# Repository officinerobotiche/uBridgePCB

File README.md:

# ![Officine Robotiche][Logo] uBridge PCB
**The first DC motor board in 4cm X 4cm** - PCB boards for uBridge

This is a project in development by [Officine Robotiche] team.

###Join on open firmware project [uNAV.X](https://github.com/officinerobotiche/uNAV.X)!!!

# Hardware features
- 2 x A4950 Full-Bridge DMOS PWM Motor Driver
  - Up to 3,5A and 40V input ( limited at 23V if used with uNav )
  - Short circuit protected
  - Over Temperature protected
- 2 x ACS712 Hall Effect-Based Linear Current Sensor IC
  - ±5A Full-Scale input Range with 185mV/A variation
  - 2,5V output @ 0.0A
- 2 connector for Encoder with Gnd, Vcc, ChA, ChB, Chz signal.
- 4 LED on outupt of H-Bridge.
- Protection diode on input.
- size: 4cm x 4cm uNav stackable.
- Matrix board with holes 2.54mm compliant.

# Available Shields
- [uNav](https://github.com/officinerobotiche/uNAVPCB)
- [uMatrix](https://github.com/officinerobotiche/)

[Officine Robotiche]:http://www.officinerobotiche.it/
[Logo]:http://2014.officinerobotiche.it/wp-content/uploads/sites/4/2014/09/ORlogoSimpleSmall.png

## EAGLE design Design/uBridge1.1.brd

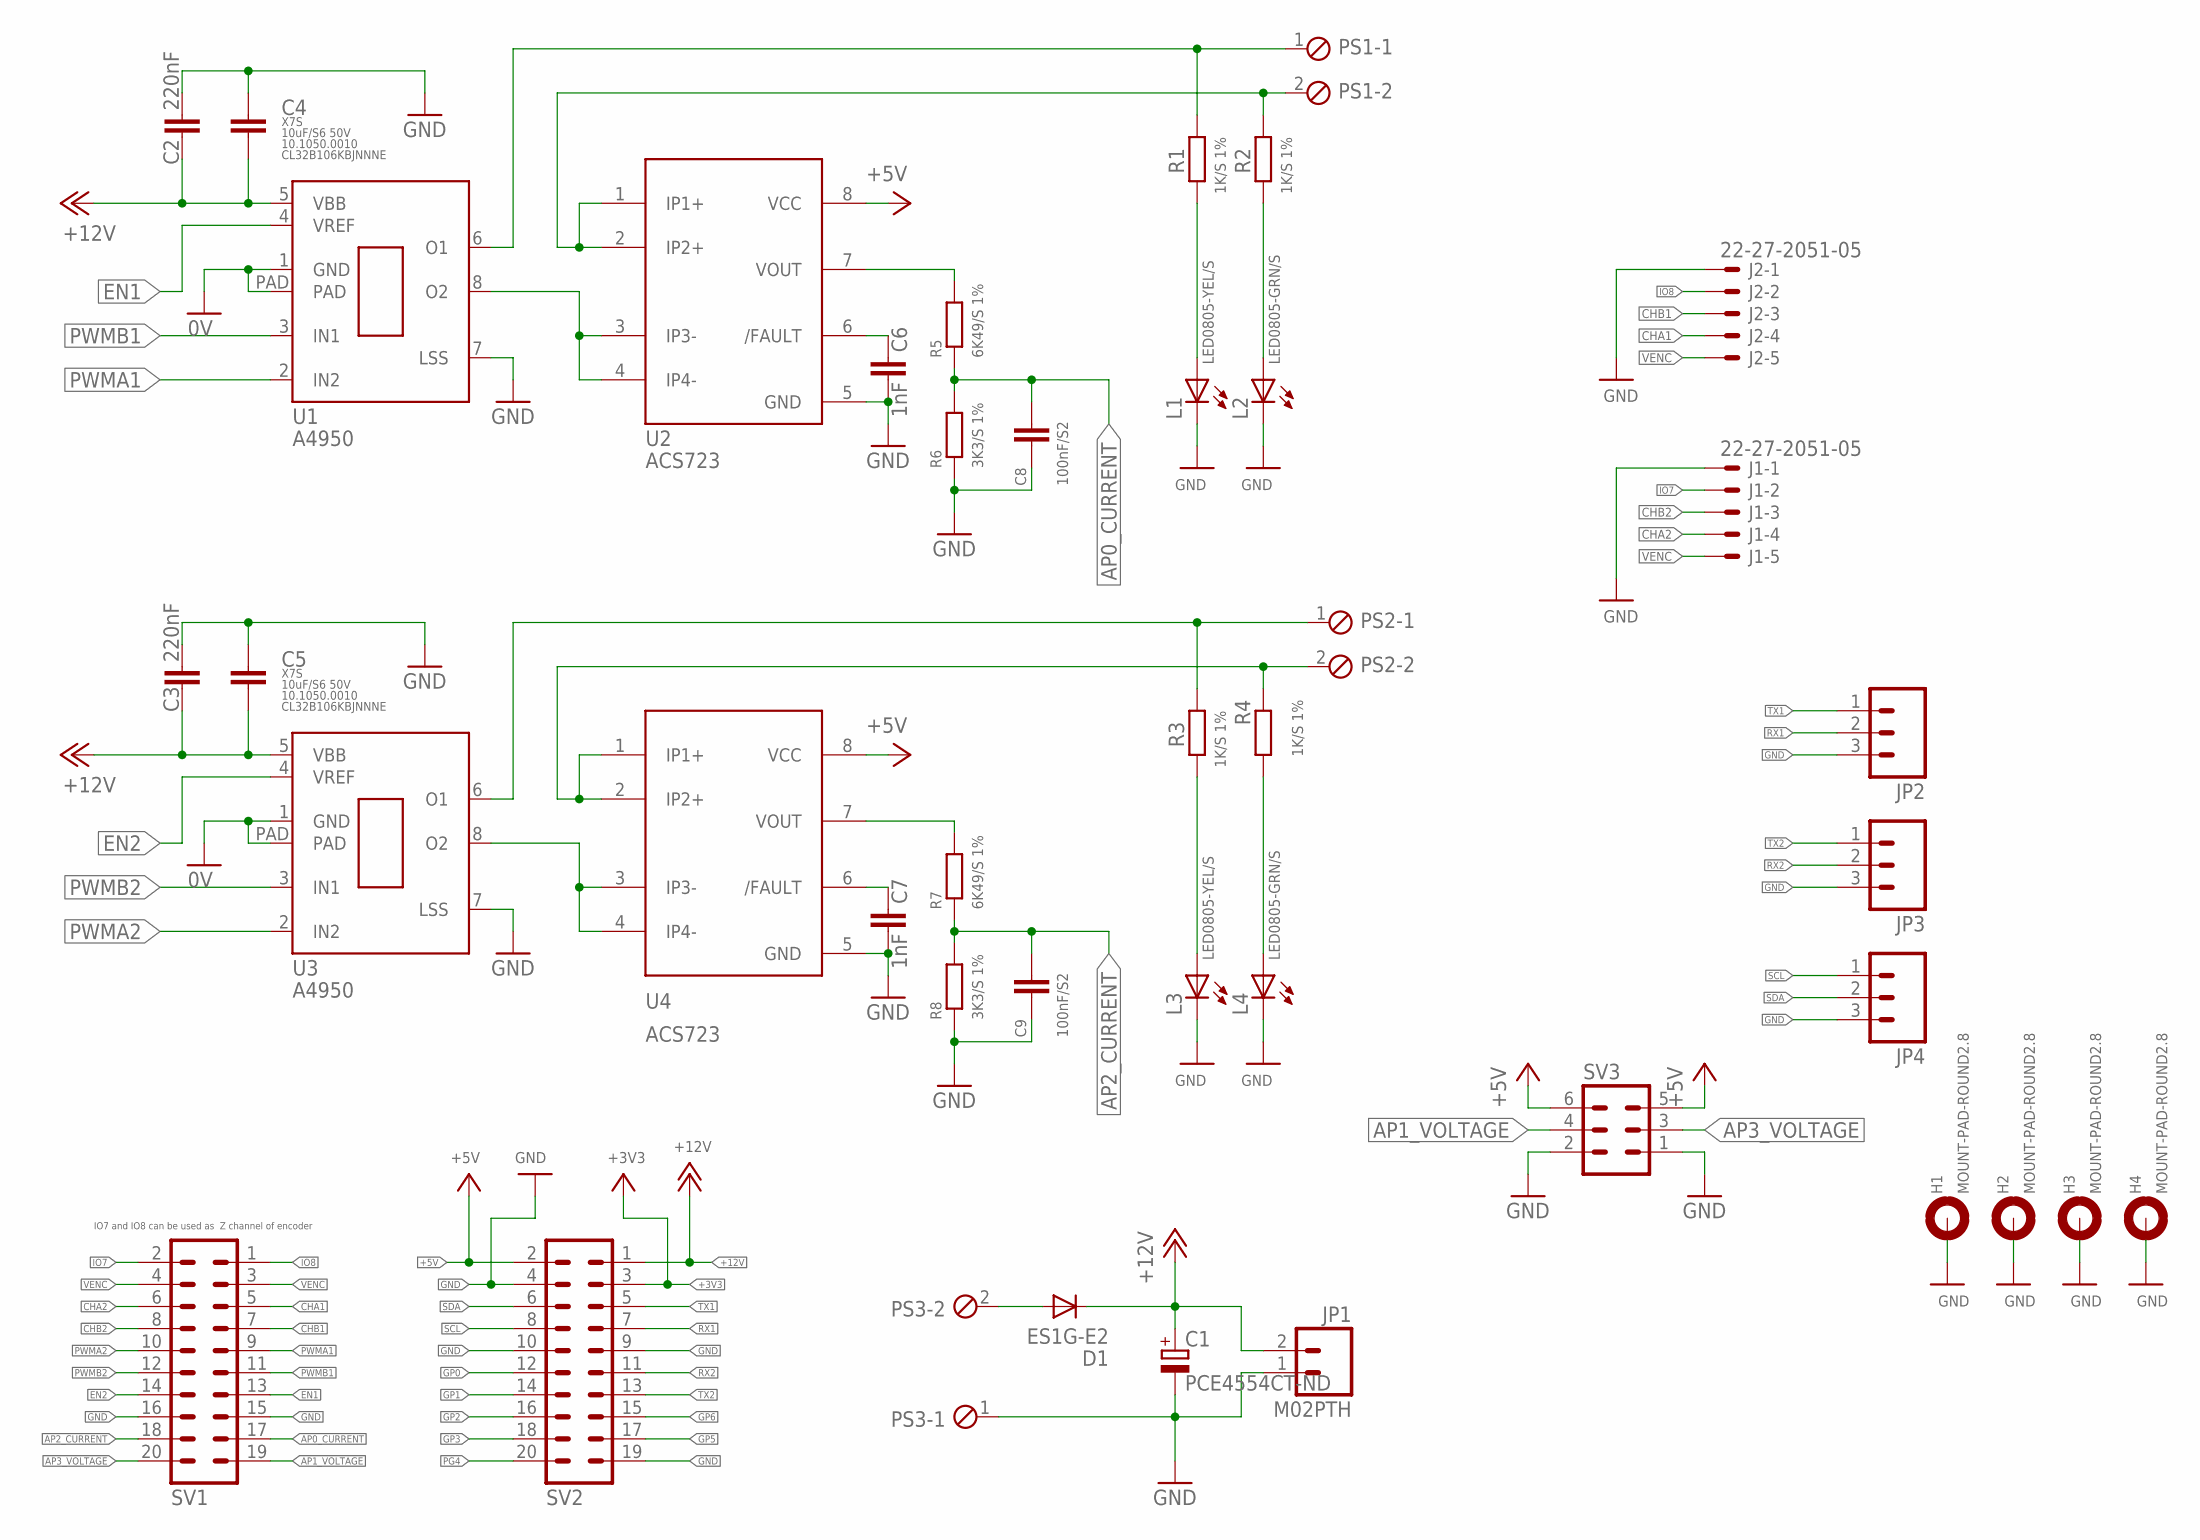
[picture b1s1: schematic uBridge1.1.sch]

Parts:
C1: PCE4554CT-ND; UD-6,3X7,7_NICHICON
C2, C3: 220nF; C0805K
C4, C5: 10uF/S6 50V; C3225
C6, C7: 1nF; C0805K
C8, C9: 100nF/S2; C0603
D1: ES1G-E2; DO214BA
H1, H2, H3, H4: MOUNT-PAD-ROUND2.8; 2,8-PAD
J1, J2: 22-27-2051-05; 6410-05
JP1: M02PTH; 1X02
JP2, JP3, JP4: M03PTH; 1X03
L1, L3: LED0805-YEL/S; CHIPLED_0805
L2, L4: LED0805-GRN/S; CHIPLED_0805
PS1, PS2, PS3: MPT2; 2POL254
R1, R2, R3, R4: 1K/S 1%; R0603
R5, R7: 6K49/S 1%; R0603
R6, R8: 3K3/S 1%; R0603
SV1, SV2: MA10-2
SV3: MA03-2
U1, U3: A4950; 8SOICN
U2, U4: ACS723; SO08

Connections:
+3V3: SV2.3
+5V: SV2.2, SV3.5, SV3.6, U2.8 (VCC), U4.8 (VCC)
+12V: C1.+, C2.2, C3.2, C4.2, C5.2, D1.C, JP1.2, SV2.1, U1.5 (VBB), U3.5 (VBB)
AP0_CURRENT: C8.1, R5.1, R6.2, SV1.17
AP1_VOLTAGE: SV1.19, SV3.4
AP2_CURRENT: C9.1, R7.1, R8.2, SV1.18
AP3_VOLTAGE: SV1.20, SV3.3
CHA1: J2.4, SV1.5
CHA2: J1.4, SV1.6
CHB1: J2.3, SV1.7
CHB2: J1.3, SV1.8
EN1: SV1.13, U1.4 (VREF)
EN2: SV1.14, U3.4 (VREF)
GND: C1.-, C2.1, C3.1, C4.1, C5.1, C6.2, C7.2, C8.2, C9.2, H1.B2,8, H2.B2,8, H3.B2,8, H4.B2,8, J1.1, J2.1, JP1.1, JP2.3, JP3.3, JP4.3, L1.C, L2.C, L3.C, L4.C, PS3.1, R6.1, R8.1, SV1.15, SV1.16, SV2.4, SV2.9, SV2.10, SV2.19, SV3.1, SV3.2, U1.1 (GND), U1.7 (LSS), U1.PAD, U2.5 (GND), U3.1 (GND), U3.7 (LSS), U3.PAD, U4.5 (GND)
GP0: SV2.12
GP1: SV2.14
GP2: SV2.16
GP3: SV2.18
GP5: SV2.17
GP6: SV2.15
IO7: J1.2, SV1.2
IO8: J2.2, SV1.1
unnamed: D1.A, PS3.2
unnamed: L1.A, R1.2
unnamed: L2.A, R2.2
unnamed: U1.8 (O2), U2.3 (IP3-), U2.4 (IP4-)
unnamed: R5.2, U2.7 (VOUT)
unnamed: U3.8 (O2), U4.3 (IP3-), U4.4 (IP4-)
unnamed: PS1.2, R2.1, U2.1 (IP1+), U2.2 (IP2+)
unnamed: PS2.2, R4.1, U4.1 (IP1+), U4.2 (IP2+)
unnamed: PS1.1, R1.1, U1.6 (O1)
unnamed: PS2.1, R3.1, U3.6 (O1)
unnamed: C6.1, U2.6 (/FAULT)
unnamed: C7.1, U4.6 (/FAULT)
unnamed: R7.2, U4.7 (VOUT)
PG4: SV2.20
PWMA1: SV1.9, U1.2 (IN2)
PWMA2: SV1.10, U3.2 (IN2)
PWMB1: SV1.11, U1.3 (IN1)
PWMB2: SV1.12, U3.3 (IN1)
RX1: JP2.2, SV2.7
RX2: JP3.2, SV2.11
SCL: JP4.1, SV2.8
SDA: JP4.2, SV2.6
TX1: JP2.1, SV2.5
TX2: JP3.1, SV2.13
VENC: J1.5, J2.5, SV1.3, SV1.4
VENC1-LD3: L3.A, R3.2
VENC2-LD4: L4.A, R4.2

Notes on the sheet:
IO7 and IO8 can be used as Z channel of encoder

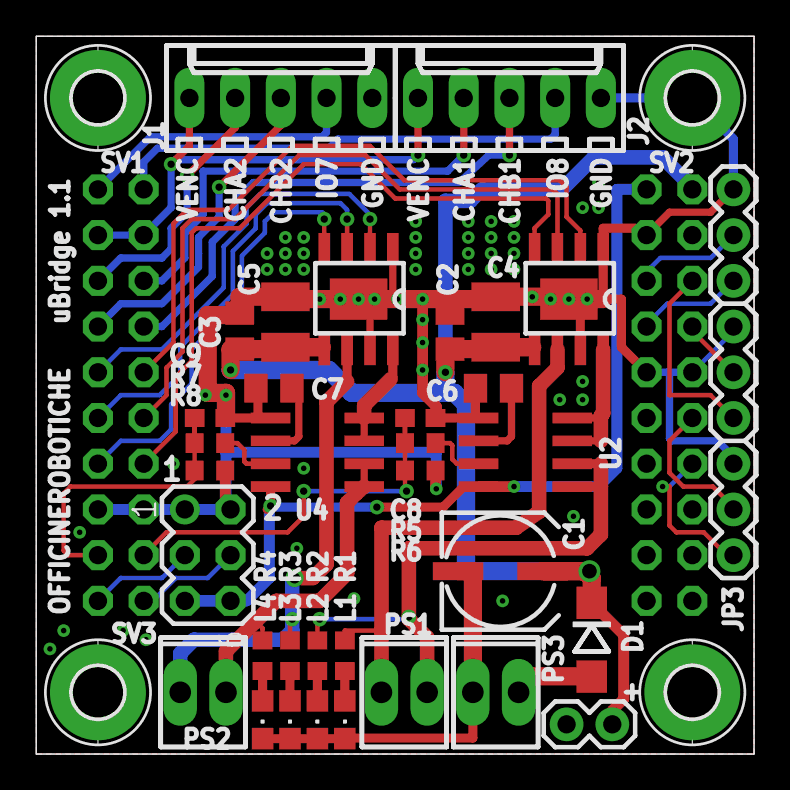
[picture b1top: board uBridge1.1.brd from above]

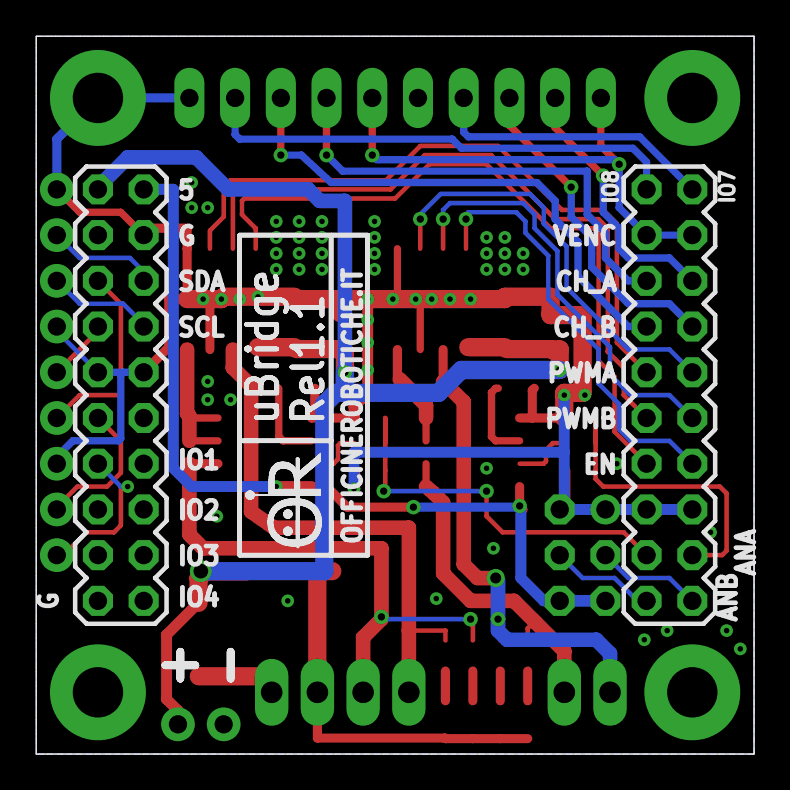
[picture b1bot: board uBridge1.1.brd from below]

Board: 2 copper layers, 39.9 x 39.9 mm, 42 parts (2 on the bottom side), 41 nets.

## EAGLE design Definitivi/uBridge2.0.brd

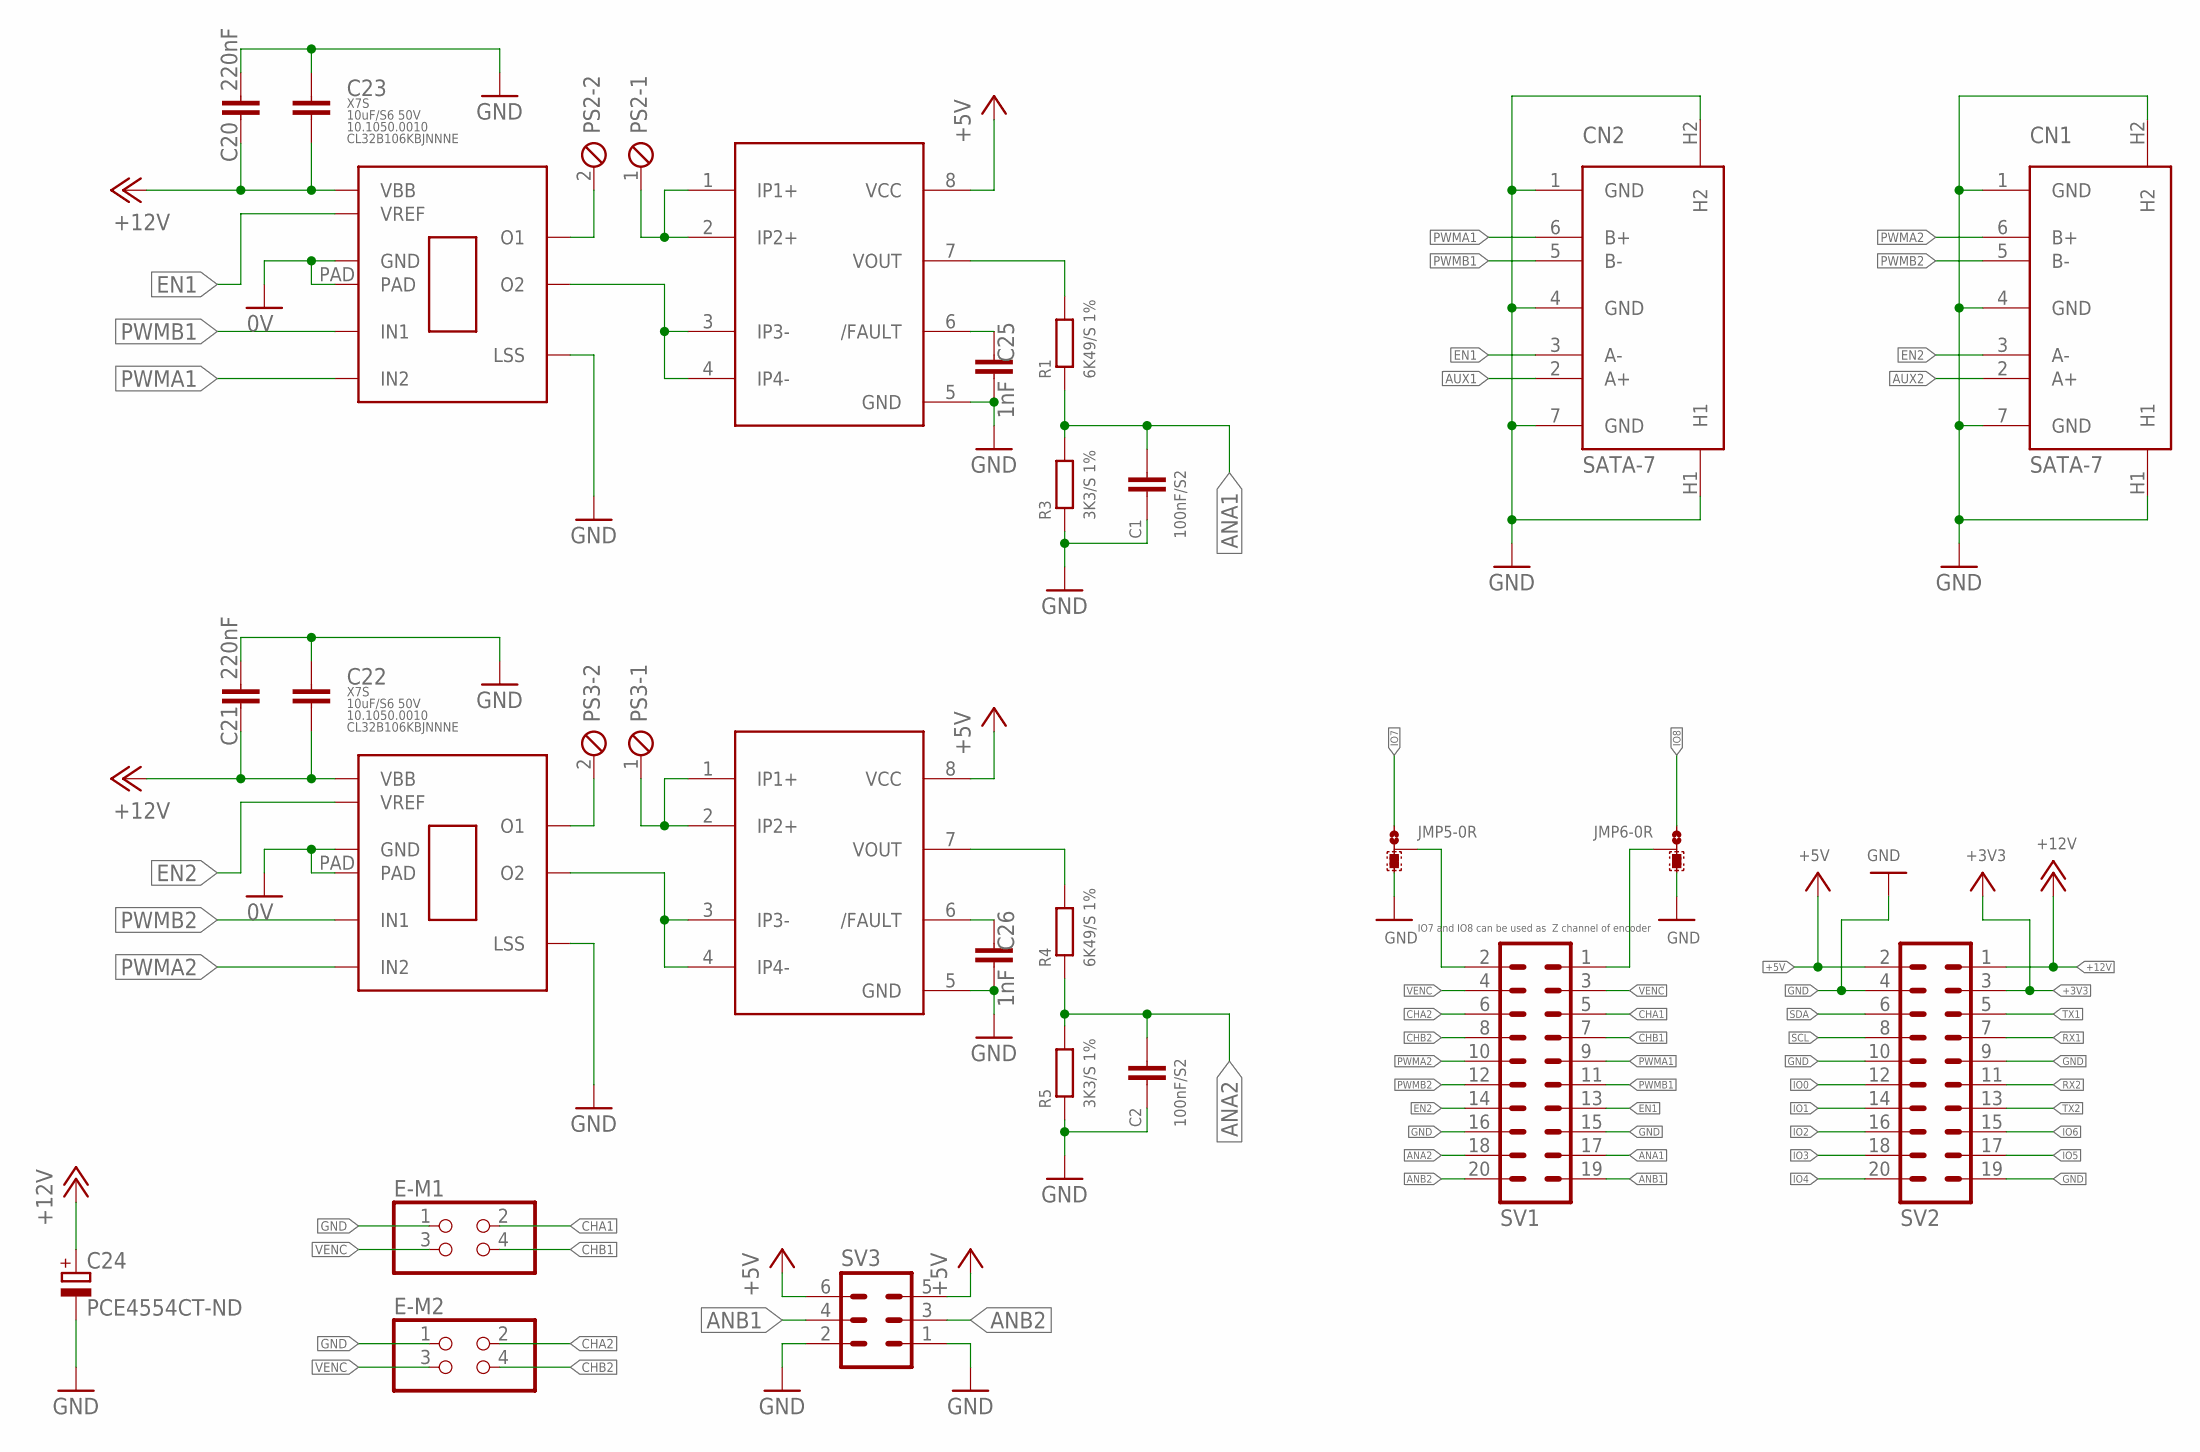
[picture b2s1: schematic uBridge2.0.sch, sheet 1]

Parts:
C1, C2: 100nF/S2; C0603
C20, C21: 220nF; C0805K
C22, C23: 10uF/S6 50V; C3225
C24: PCE4554CT-ND; UD-6,3X7,7_NICHICON
C25, C26: 1nF; C0805K
CN1, CN2: SATA-7; SATA-5607-5102-SH
E-M1, E-M2: PINHD-2X2; 2X02
JMP5, JMP6: 0R-JUMPC; C0R-JMP
PS2, PS3: MPT2; 2POL254
R1, R4: 6K49/S 1%; R0603
R3, R5: 3K3/S 1%; R0603
SV1, SV2: MA10-2
SV3: MA03-2
U$2, U$3: A4950; SOICN
U$4, U$5: ACS723; SO08

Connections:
+3V3: SV2.3
+5V: SV2.2, SV3.5, SV3.6, U$4.8 (VCC), U$5.8 (VCC); also elsewhere on the board
+12V: C20.2, C21.2, C22.2, C23.2, C24.+, SV2.1, U$2.5VCC (VBB), U$3.5VCC (VBB); also elsewhere on the board
ANA1: C1.1, R1.1, R3.2, SV1.17
ANA2: C2.1, R4.1, R5.2, SV1.18
ANB1: SV1.19, SV3.4
ANB2: SV1.20, SV3.3
AUX1: CN2.2 (A+)
AUX2: CN1.2 (A+)
CHA1: E-M1.2, SV1.5
CHA2: E-M2.2, SV1.6
CHB1: E-M1.4, SV1.7
CHB2: E-M2.4, SV1.8
EN1: CN2.3 (A-), SV1.13, U$2.4CS (VREF)
EN2: CN1.3 (A-), SV1.14, U$3.4CS (VREF)
GND: C1.2, C2.2, C20.1, C21.1, C22.1, C23.1, C24.-, C25.2, C26.2, CN1.1 (GND), CN1.4 (GND), CN1.7 (GND), CN1.H1, CN1.H2, CN2.1 (GND), CN2.4 (GND), CN2.7 (GND), CN2.H1, CN2.H2, E-M1.1, E-M2.1, JMP5.3, JMP6.3, R3.1, R5.1, SV1.15, SV1.16, SV2.4, SV2.9, SV2.10, SV2.19, SV3.1, SV3.2, U$2.1VIN (GND), U$2.7BOOT (LSS), U$2.PAD, U$3.1VIN (GND), U$3.7BOOT (LSS), U$3.PAD, U$4.5 (GND), U$5.5 (GND); also elsewhere on the board
IO0: SV2.12
IO1: SV2.14
IO2: SV2.16
IO3: SV2.18
IO4: SV2.20
IO5: SV2.17
IO6: SV2.15
IO7: JMP5.1
IO8: JMP6.1
unnamed: R1.2, U$4.7 (VOUT)
unnamed: R4.2, U$5.7 (VOUT)
unnamed: JMP5.2, SV1.2
unnamed: U$2.8SW (O2), U$4.3 (IP3-), U$4.4 (IP4-)
unnamed: U$3.8SW (O2), U$5.3 (IP3-), U$5.4 (IP4-)
unnamed: PS2.1, U$4.1 (IP1+), U$4.2 (IP2+)
unnamed: JMP6.2, SV1.1
unnamed: PS3.1, U$5.1 (IP1+), U$5.2 (IP2+)
unnamed: PS2.2, U$2.6GND (O1)
unnamed: PS3.2, U$3.6GND (O1)
unnamed: C25.1, U$4.6 (/FAULT)
unnamed: C26.1, U$5.6 (/FAULT)
PWMA1: CN2.6 (B+), SV1.9, U$2.2TON (IN2)
PWMA2: CN1.6 (B+), SV1.10, U$3.2TON (IN2)
PWMB1: CN2.5 (B-), SV1.11, U$2.3EN (IN1)
PWMB2: CN1.5 (B-), SV1.12, U$3.3EN (IN1)
RX1: SV2.7
RX2: SV2.11
SCL: SV2.8
SDA: SV2.6
TX1: SV2.5
TX2: SV2.13
VENC: E-M1.3, E-M2.3, SV1.3, SV1.4

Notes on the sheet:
IO7 and IO8 can be used as Z channel of encoder

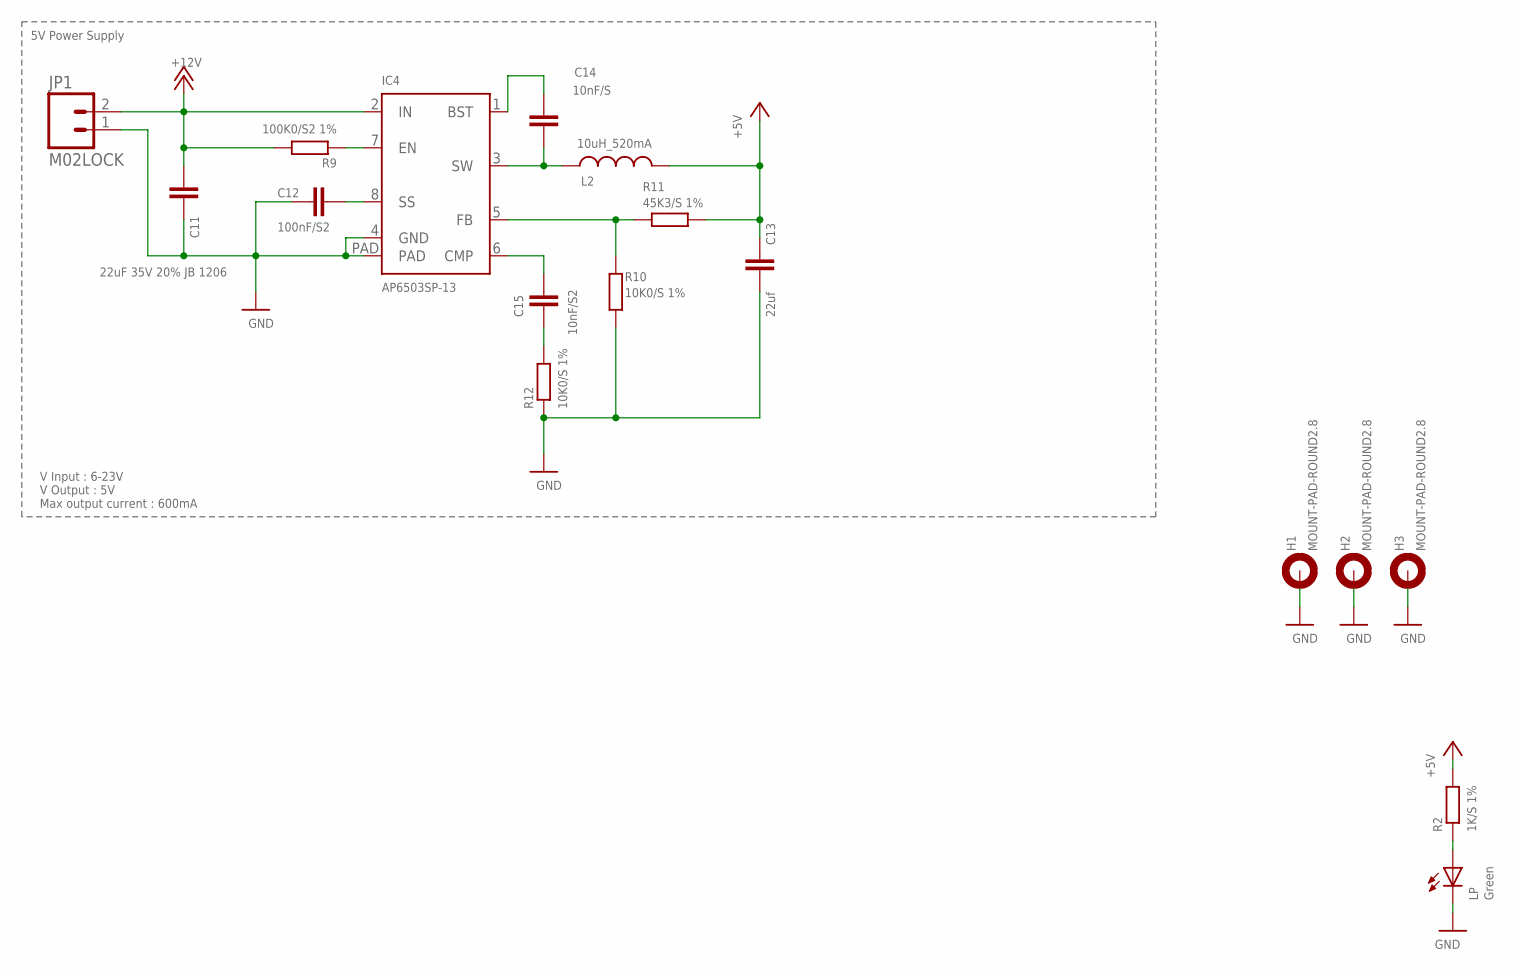
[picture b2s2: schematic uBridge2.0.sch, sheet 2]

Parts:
C11: 22uF 35V 20% JB 1206; C1206
C12: 100nF/S2; C0603
C13: 22uf; C1206
C14: 10nF/S; C0603
C15: 10nF/S2; C0603
H1, H2, H3: MOUNT-PAD-ROUND2.8; 2,8-PAD
IC4: AP6503SP-13; SO-8EP
JP1: M02LOCK; 1X02_LOCK
L2: 10uH_520mA; 1210
LP: Green; CHIPLED_0805
R2: 1K/S 1%; R0603
R9: 100K0/S2 1%; R0603
R10, R12: 10K0/S 1%; R0603
R11: 45K3/S 1%; R0603

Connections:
+5V: C13.1, L2.2, R2.2, R11.2; also elsewhere on the board
+12V: C11.1, IC4.2 (IN), JP1.2, R9.2; also elsewhere on the board
GND: C11.2, C12.2, C13.2, H1.B2,8, H2.B2,8, H3.B2,8, IC4.4 (GND), IC4.PAD, JP1.1, LP.C, R10.2, R12.1; also elsewhere on the board
unnamed: C14.1, IC4.1 (BST)
unnamed: LP.A, R2.1
unnamed: IC4.7 (EN), R9.1
unnamed: C12.1, IC4.8 (SS)
unnamed: IC4.5 (FB), R10.1, R11.1
unnamed: C14.2, IC4.3 (SW), L2.1
unnamed: C15.1, IC4.6 (CMP)
unnamed: C15.2, R12.2

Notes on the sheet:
5V Power Supply
V Input : 6-23V V Output : 5V Max output current : 600mA

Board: 2 copper layers, 45 parts (4 on the bottom side), 38 nets, no tracks yet.

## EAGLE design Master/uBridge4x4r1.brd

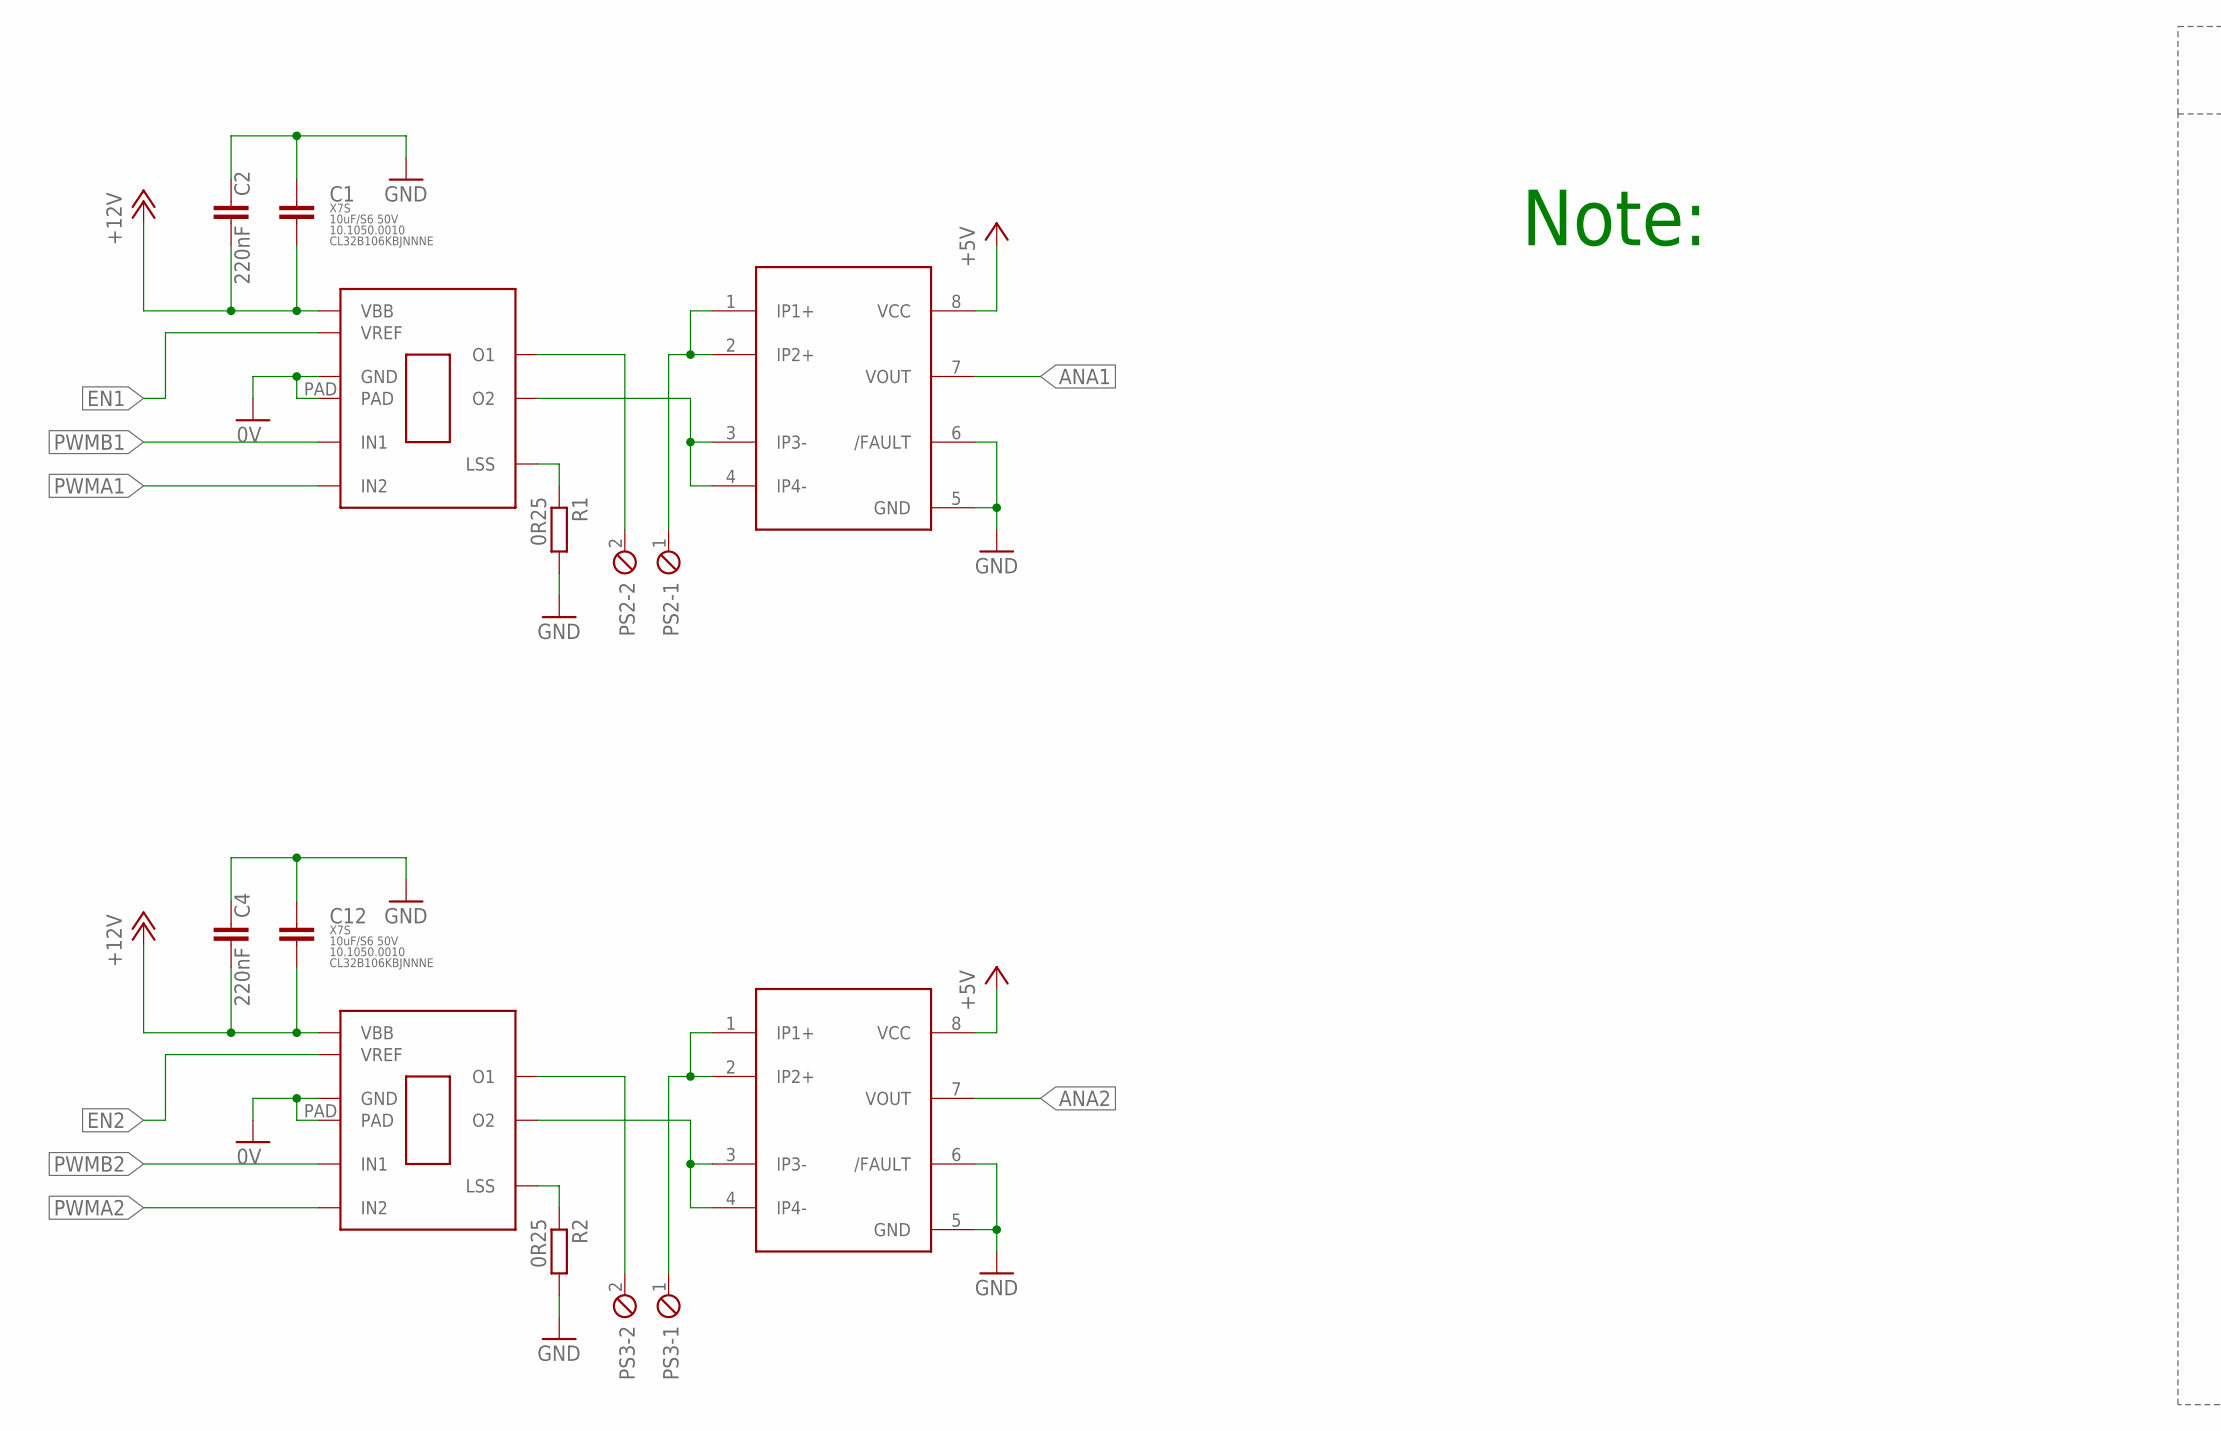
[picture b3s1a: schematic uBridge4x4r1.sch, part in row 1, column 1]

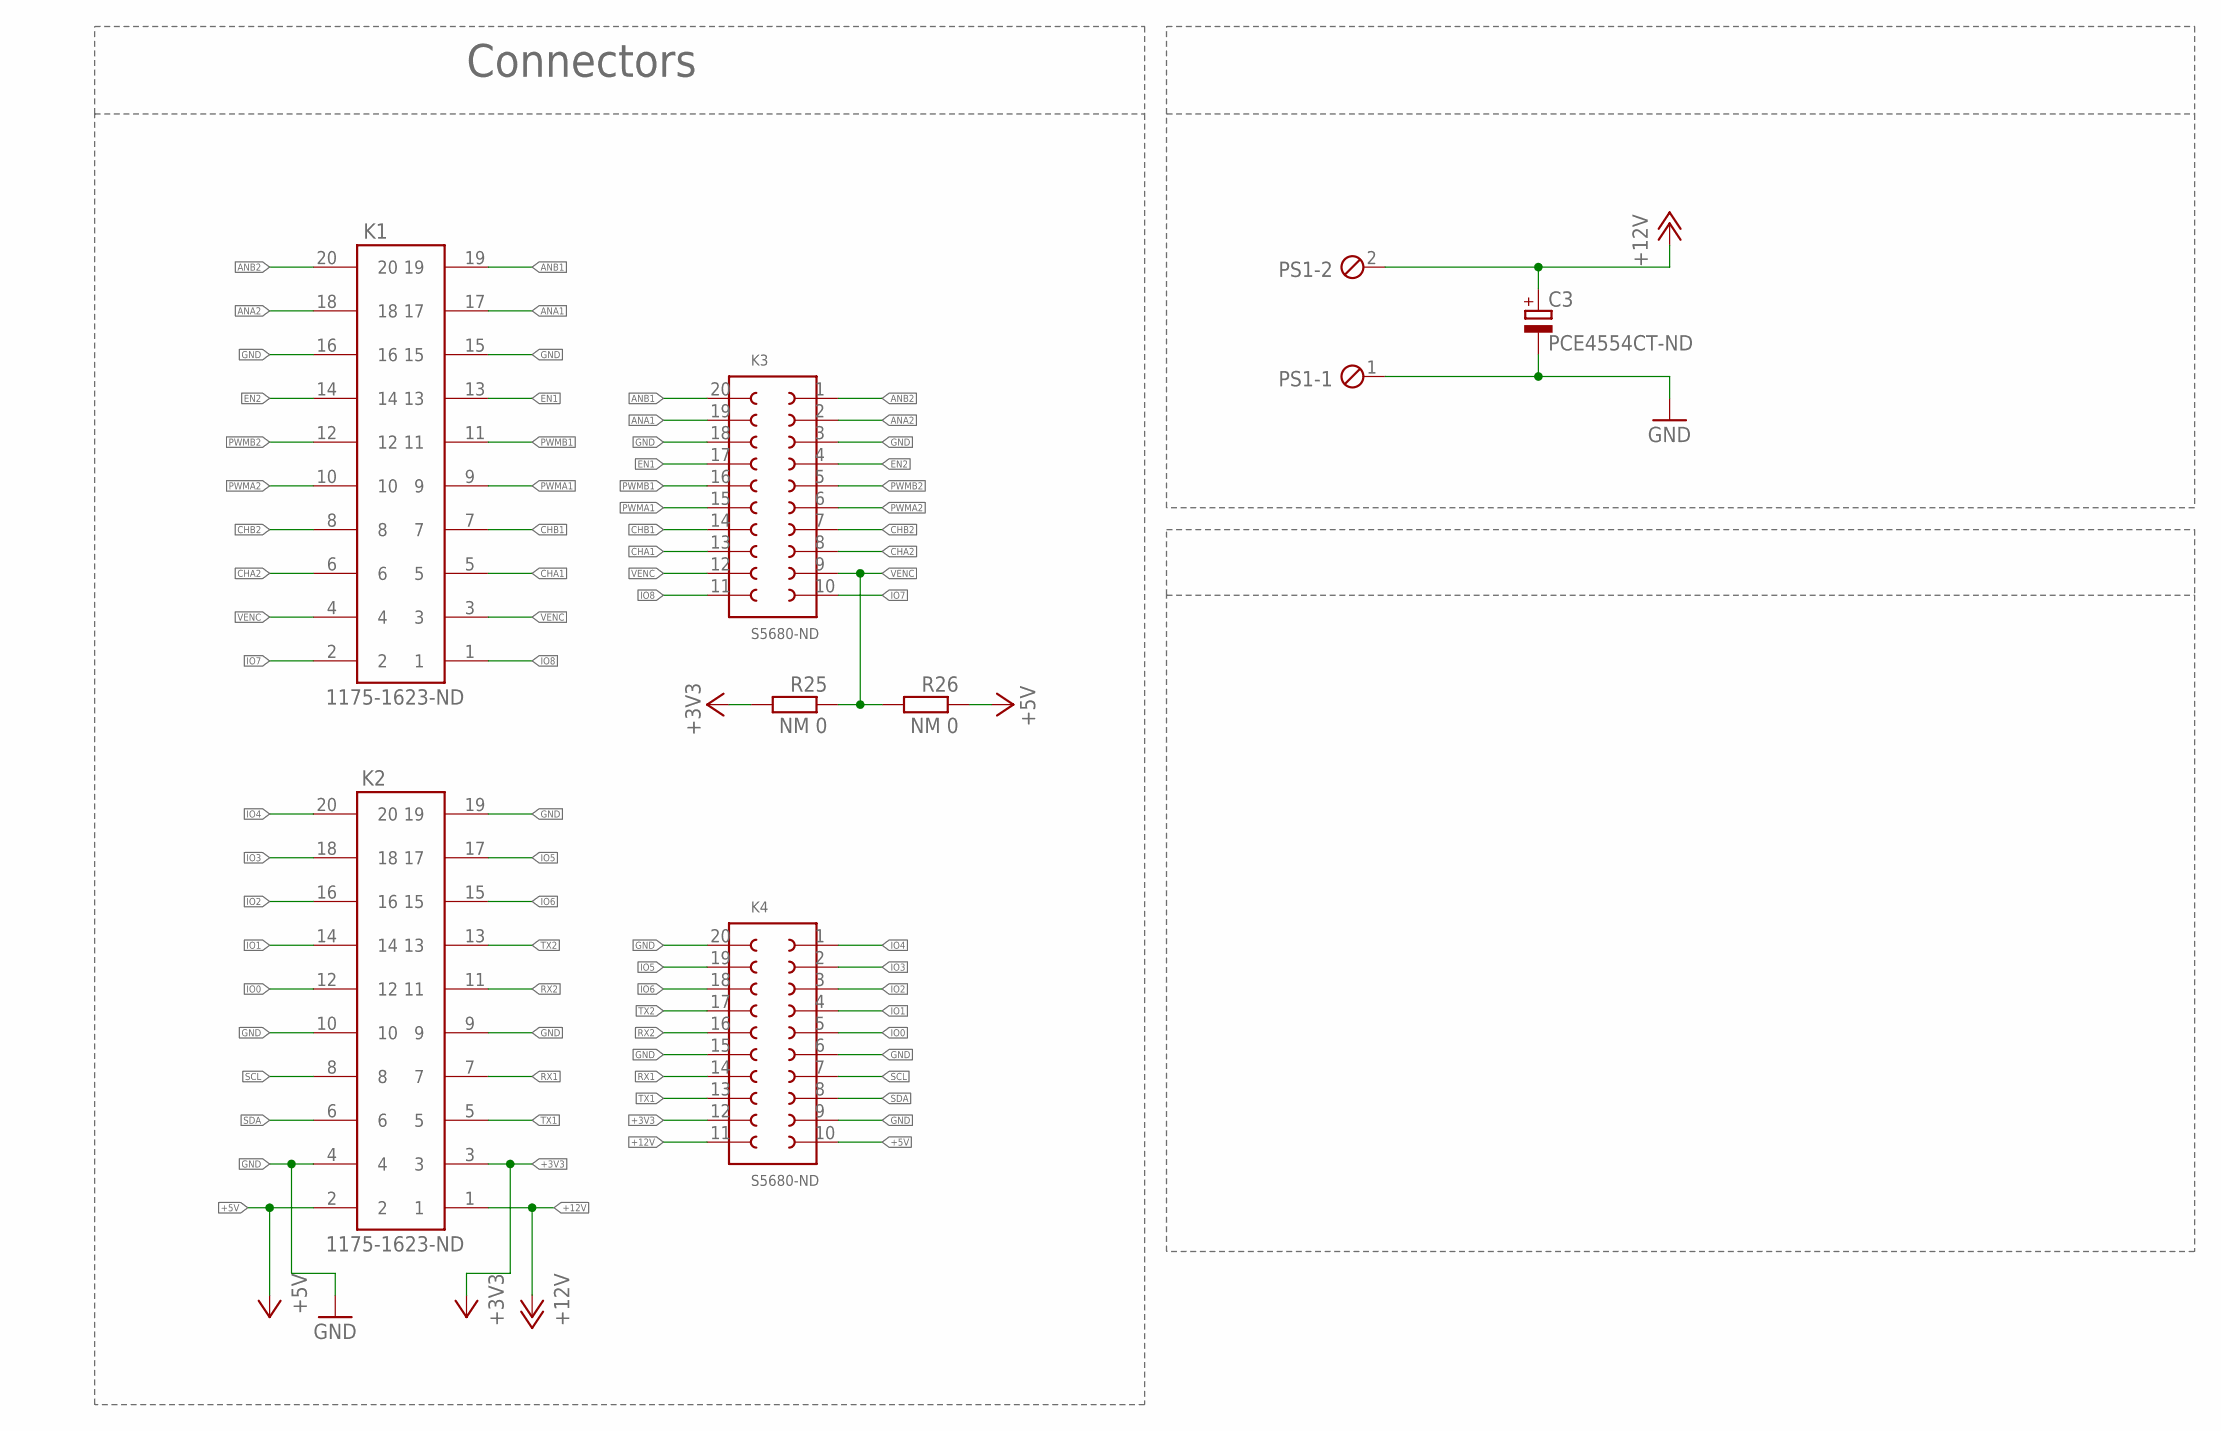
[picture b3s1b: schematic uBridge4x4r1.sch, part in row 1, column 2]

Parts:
C1, C12: 10uF/S6 50V; C3225
C2, C4: 220nF; C0805K
C3: PCE4554CT-ND; UD-6,3X7,7_NICHICON
K1, K2: 1175-1623-ND; 612X2020621
K3, K4: S5680-ND; 61002021821
PS1, PS2, PS3: MPT2; 2POL254
R1, R2: 0R25; R1206
R25, R26: NM 0; R0603
U$1, U$2: A4950; SOICN
U$3, U$4: ACS723; SO08

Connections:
+3V3: K2.3, K4.12, R25.2
+5V: K2.2, K4.10, R26.1, U$3.8 (VCC), U$4.8 (VCC)
+12V: C1.2, C2.2, C3.+, C4.2, C12.2, K2.1, K4.11, PS1.2, U$1.5VCC (VBB), U$2.5VCC (VBB)
ANA1: K1.17, K3.19, U$3.7 (VOUT)
ANA2: K1.18, K3.2, U$4.7 (VOUT)
ANB1: K1.19, K3.20
ANB2: K1.20, K3.1
CHA1: K1.5, K3.13
CHA2: K1.6, K3.8
CHB1: K1.7, K3.14
CHB2: K1.8, K3.7
EN1: K1.13, K3.17, U$1.4CS (VREF)
EN2: K1.14, K3.4, U$2.4CS (VREF)
GND: C1.1, C2.1, C3.-, C4.1, C12.1, K1.15, K1.16, K2.4, K2.9, K2.10, K2.19, K3.3, K3.18, K4.6, K4.9, K4.15, K4.20, PS1.1, R1.2, R2.2, U$1.1VIN (GND), U$1.PAD, U$2.1VIN (GND), U$2.PAD, U$3.5 (GND), U$3.6 (/FAULT), U$4.5 (GND), U$4.6 (/FAULT)
IO0: K2.12, K4.5
IO1: K2.14, K4.4
IO2: K2.16, K4.3
IO3: K2.18, K4.2
IO4: K2.20, K4.1
IO5: K2.17, K4.19
IO6: K2.15, K4.18
IO7: K1.2, K3.10
IO8: K1.1, K3.11
unnamed: R2.1, U$2.7BOOT (LSS)
unnamed: PS3.2, U$2.6GND (O1)
unnamed: U$2.8SW (O2), U$4.3 (IP3-), U$4.4 (IP4-)
unnamed: PS2.1, U$3.1 (IP1+), U$3.2 (IP2+)
unnamed: PS2.2, U$1.6GND (O1)
unnamed: PS3.1, U$4.1 (IP1+), U$4.2 (IP2+)
unnamed: R1.1, U$1.7BOOT (LSS)
unnamed: U$1.8SW (O2), U$3.3 (IP3-), U$3.4 (IP4-)
PWMA1: K1.9, K3.15, U$1.2TON (IN2)
PWMA2: K1.10, K3.6, U$2.2TON (IN2)
PWMB1: K1.11, K3.16, U$1.3EN (IN1)
PWMB2: K1.12, K3.5, U$2.3EN (IN1)
RX1: K2.7, K4.14
RX2: K2.11, K4.16
SCL: K2.8, K4.7
SDA: K2.6, K4.8
TX1: K2.5, K4.13
TX2: K2.13, K4.17
VENC: K1.3, K1.4, K3.9, K3.12, R25.1, R26.2

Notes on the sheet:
Connectors
Note:

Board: 2 copper layers, 20 parts (2 on the bottom side), 42 nets, no tracks yet.

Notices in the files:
parts and their libraries:
SparkFun-Passives: Licensing: Creative Commons ShareAlike 4.0 International - https://creativecommons.org/licenses/by-sa/4.0
Wuerth_Elektronik_eiCan_Wire_to_Board_Co: Copyright: Würth Elektronik
